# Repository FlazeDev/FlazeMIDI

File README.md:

# FlazeMIDI

This is a simple 25 key MIDI Controller with 3 rotary encoders. I used a Raspberry Pi Pico as the brain for this MIDI Controller.

## Bill of Materials (BOM)
|BOM for FlazeMIDI|FIELD2                         |FIELD3                                                                                     |FIELD4                      |FIELD5                                     |FIELD6                          |
|-----------------|-------------------------------|-------------------------------------------------------------------------------------------|----------------------------|-------------------------------------------|--------------------------------|
|S.No             |Name Of Part                   |Link                                                                                       |Price per item(W/o Shipping)|Quantity                                   |Total Cost Of Item(W/O Shipping)|
|1                |Raspberry pi pico              |https://robu.in/product/raspberry-pi-pico-with-headers/                                    |499.00 INR                  |1                                          |499.00 INR                      |
|2                |1N4148 diodes(pack of 50)      |https://www.amazon.in/gp/product/B0B53NV1QC/ref=ox_sc_act_title_1?smid=A3OFZYSBUU01KL&psc=1|99.00 INR                   |1                                          |99.00 INR                       |
|3                |Switches(pack of 10)           |https://stackskb.com/store/click-inc-hp-switch-pack-of-10-pre-order/                       |180.00 INR                  |3                                          |540.00 INR                      |
|4                |EC11 Rotary Encoders(pack of 5)|https://stackskb.com/store/click-inc-hp-switch-pack-of-10-pre-order/                       |696.00 INR                  |1                                          |696.00 INR                      |
|5                |Keycaps(pack of 5)             |https://meckeys.com/shop/accessories/keyboard-accessories/keycaps/blank-dsa-keycaps-1u/    |95.00 INR                   |5                                          |475.00 INR                      |
|6                |PCB Fabrication                |jlcpcb.com                                                                                 |976.96 INR                  |1                                          |976.96 INR                      |
|7                |PCB Shipping                   |jlcpcb.com                                                                                 |1,091.73 INR                |1                                          |1,091.73 INR                    |
|8                |M3x4mm Heatsets                |I already have it                                                                          |0.00 INR                    |4                                          |0.00 INR                        |
|9                |M3x4mm screws                  |I already have it                                                                          |0.00 INR                    |4                                          |0.00 INR                        |
|                 |                               |                                                                                           |                            |                                           |                                |
|                 |                               |                                                                                           |                            |                                           |                                |
|                 |                               |                                                                                           |                            |                                           |                                |
|                 |                               |                                                                                           |                            |                                           |                                |
|                 |                               |                                                                                           |                            |                                           |                                |
|                 |                               |                                                                                           |                            |                                           |                                |
|                 |                               |                                                                                           |                            |Total INR(only including  Shipping for pcb)|4,377.69 INR                    |
|                 |                               |                                                                                           |                            |Total USD                                  |$48.15                          |

### Total Project Cost
$48.15 without shipping. Shipping should take another $10 max.
Total Project cost: **$58**

## Schematic & PCB

I made the pcb in kicad

## 3d Case

The case consists of 3 parts, the top cover, bottom cover and a stand that attaches to the bottom. Everything is connected using m3 heat set inserts and screws.
I made the case in onshape. here's the link for the onshape project:- https://cad.onshape.com/documents/0f47473beb05ba1bc00654df/w/e1cbcdd202a0a0f5e24ed7bd/e/dbeb9d6fbd234f685e1c68c6

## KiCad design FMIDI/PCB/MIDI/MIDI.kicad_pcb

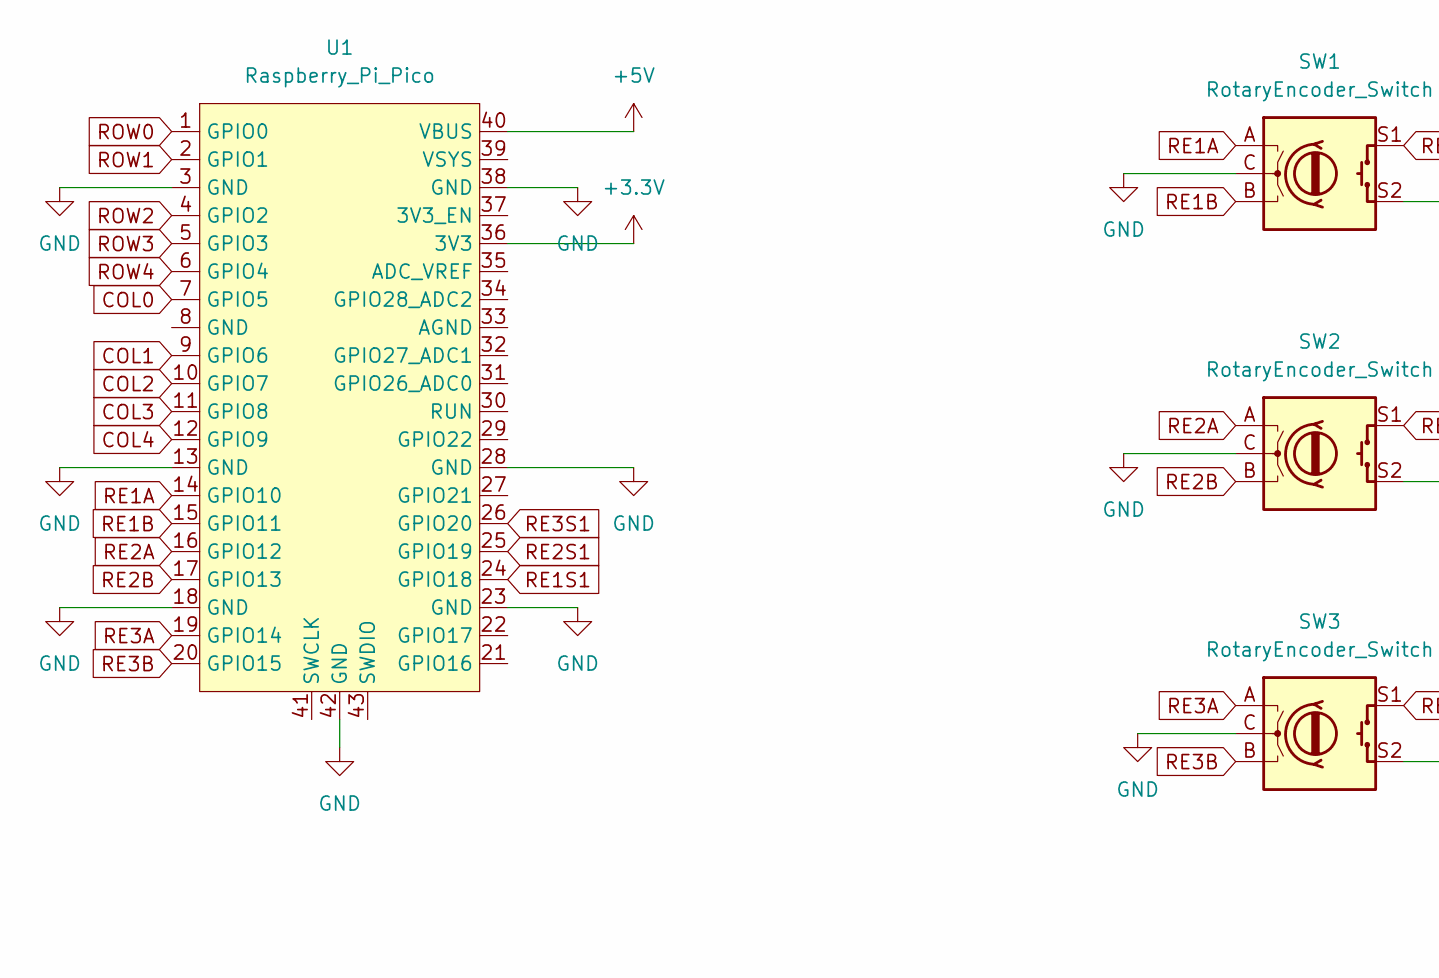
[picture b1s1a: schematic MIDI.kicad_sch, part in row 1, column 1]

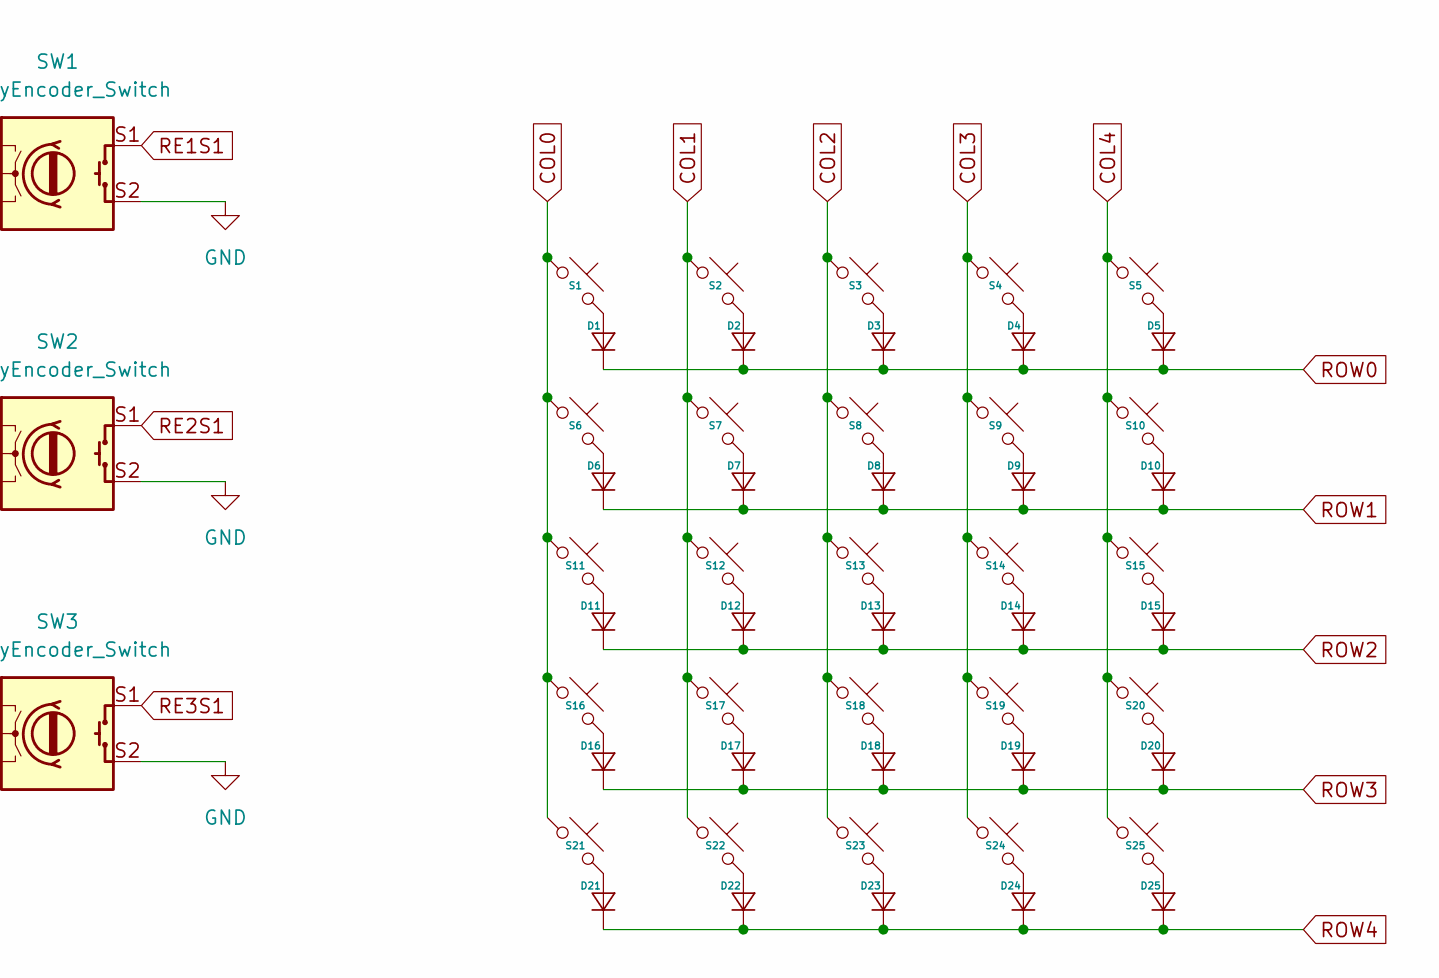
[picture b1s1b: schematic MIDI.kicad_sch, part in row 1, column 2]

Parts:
D1, D2, D3, D4, D5, D6, D7, D8, D9, D10, D11, D12, D13, D14, D15, D16, D17, D18, D19, D20, D21, D22, D23, D24, D25: D_DO-35_SOD27_P7.62mm_Horizontal
S1, S2, S3, S4, S5, S6, S7, S8, S9, S10, S11, S12, S13, S14, S15, S16, S17, S18, S19, S20, S21, S22, S23, S24, S25: MX_PCB_1.00u
SW1, SW2, SW3: RotaryEncoder_Switch; Encoder_EC11_MX
U1: Raspberry_Pi_Pico

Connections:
+3.3V: U1.36 (3V3)
+5V: U1.40 (VBUS)
COL0: S1.1, S6.1, S11.1, S16.1, S21.1, U1.7 (GPIO5)
COL1: S2.1, S7.1, S12.1, S17.1, S22.1, U1.9 (GPIO6)
COL2: S3.1, S8.1, S13.1, S18.1, S23.1, U1.10 (GPIO7)
COL3: S4.1, S9.1, S14.1, S19.1, S24.1, U1.11 (GPIO8)
COL4: S5.1, S10.1, S15.1, S20.1, S25.1, U1.12 (GPIO9)
GND: SW1.C, SW1.S2, SW2.C, SW2.S2, SW3.C, SW3.S2, U1.3 (GND), U1.13 (GND), U1.18 (GND), U1.23 (GND), U1.28 (GND), U1.38 (GND), U1.42 (GND)
unnamed: D1.2 (A), S1.2
unnamed: D2.2 (A), S2.2
unnamed: D3.2 (A), S3.2
unnamed: D4.2 (A), S4.2
unnamed: D5.2 (A), S5.2
unnamed: D6.2 (A), S6.2
unnamed: D7.2 (A), S7.2
unnamed: D8.2 (A), S8.2
unnamed: D9.2 (A), S9.2
unnamed: D10.2 (A), S10.2
unnamed: D11.2 (A), S11.2
unnamed: D12.2 (A), S12.2
unnamed: D13.2 (A), S13.2
unnamed: D14.2 (A), S14.2
unnamed: D15.2 (A), S15.2
unnamed: D16.2 (A), S16.2
unnamed: D17.2 (A), S17.2
unnamed: D18.2 (A), S18.2
unnamed: D19.2 (A), S19.2
unnamed: D20.2 (A), S20.2
unnamed: D21.2 (A), S21.2
unnamed: D22.2 (A), S22.2
unnamed: D23.2 (A), S23.2
unnamed: D24.2 (A), S24.2
unnamed: D25.2 (A), S25.2
RE1A: SW1.A, U1.14 (GPIO10)
RE1B: SW1.B, U1.15 (GPIO11)
RE1S1: SW1.S1, U1.24 (GPIO18)
RE2A: SW2.A, U1.16 (GPIO12)
RE2B: SW2.B, U1.17 (GPIO13)
RE2S1: SW2.S1, U1.25 (GPIO19)
RE3A: SW3.A, U1.19 (GPIO14)
RE3B: SW3.B, U1.20 (GPIO15)
RE3S1: SW3.S1, U1.26 (GPIO20)
ROW0: D1.1 (K), D2.1 (K), D3.1 (K), D4.1 (K), D5.1 (K), U1.1 (GPIO0)
ROW1: D6.1 (K), D7.1 (K), D8.1 (K), D9.1 (K), D10.1 (K), U1.2 (GPIO1)
ROW2: D11.1 (K), D12.1 (K), D13.1 (K), D14.1 (K), D15.1 (K), U1.4 (GPIO2)
ROW3: D16.1 (K), D17.1 (K), D18.1 (K), D19.1 (K), D20.1 (K), U1.5 (GPIO3)
ROW4: D21.1 (K), D22.1 (K), D23.1 (K), D24.1 (K), D25.1 (K), U1.6 (GPIO4)

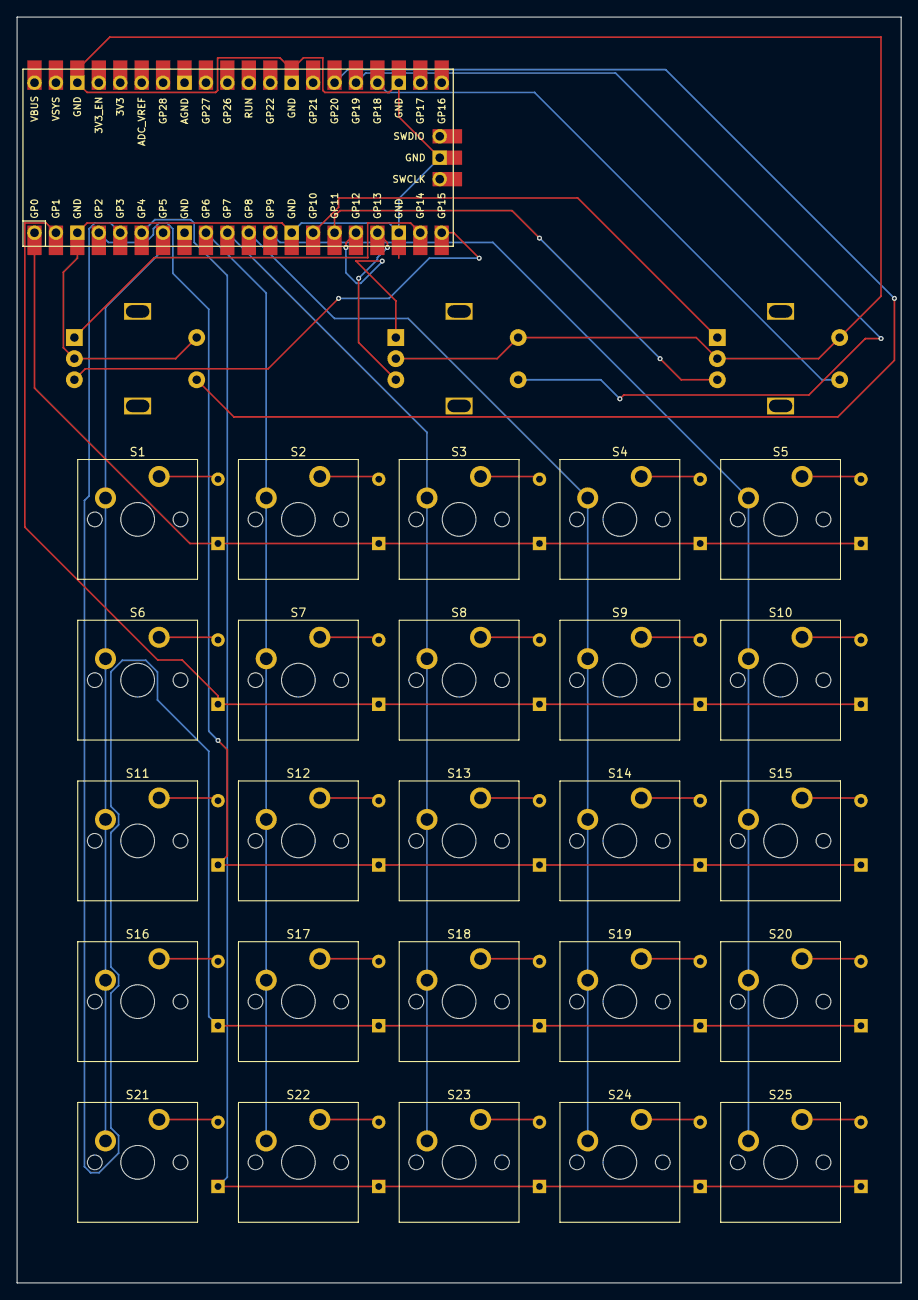
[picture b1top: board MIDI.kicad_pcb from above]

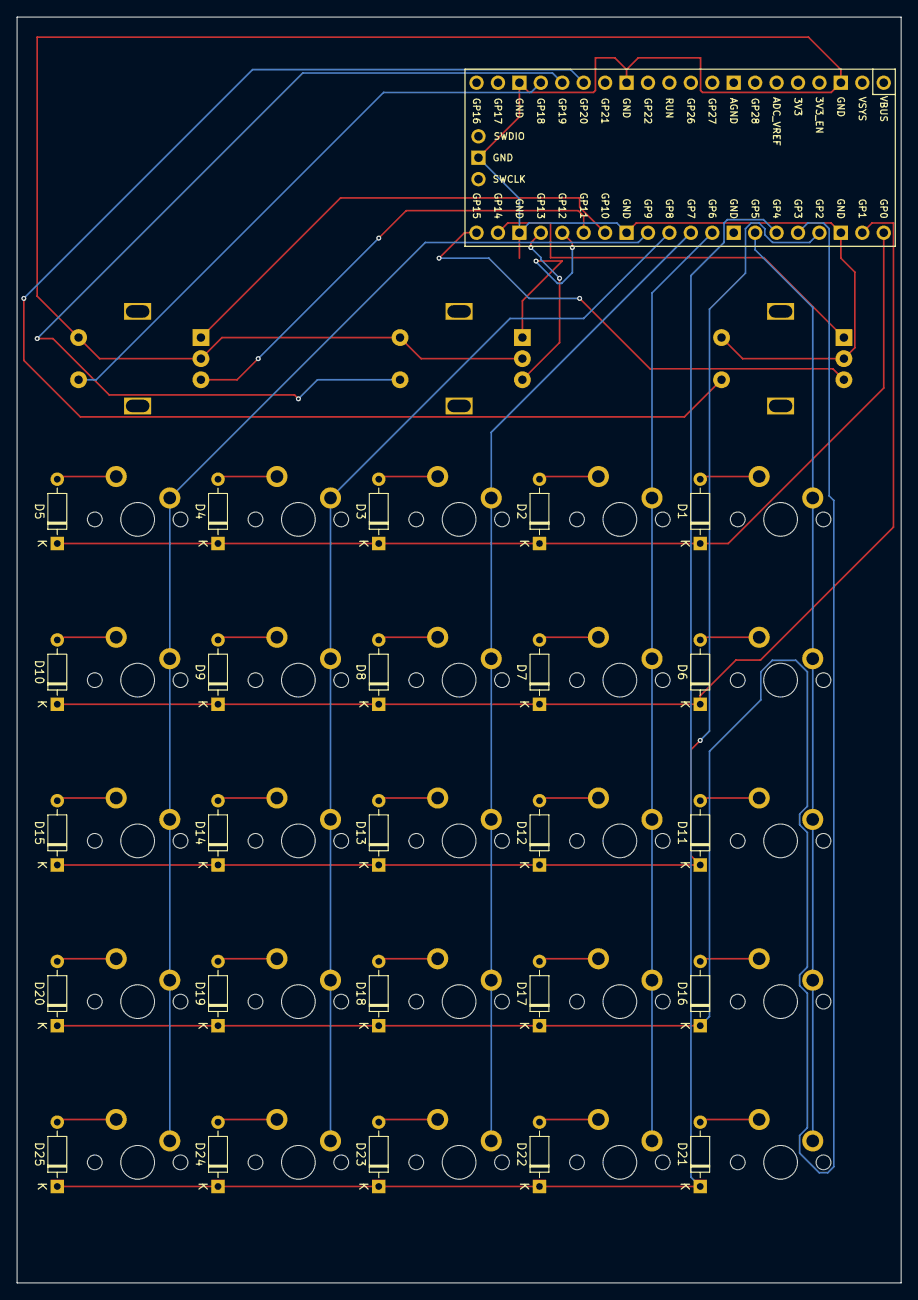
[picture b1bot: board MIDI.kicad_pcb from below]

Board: 2 copper layers, 104.8 x 150.0 mm, 54 parts (25 on the bottom side), 45 nets.

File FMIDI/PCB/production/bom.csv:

Designator,Footprint,Quantity,Value,LCSC Part #
"D1, D10, D11, D12, D13, D14, D15, D16, D17, D18, D19, D2, D20, D21, D22, D23, D24, D25, D3, D4, D5, D6, D7, D8, D9",D_DO-35_SOD27_P7.62mm_Horizontal,25,~,
"S1, S10, S11, S12, S13, S14, S15, S16, S17, S18, S19, S2, S20, S21, S22, S23, S24, S25, S3, S4, S5, S6, S7, S8, S9",MX_PCB_1.00u,25,~,
"SW1, SW2, SW3",Encoder_EC11_MX,3,RotaryEncoder_Switch,
U1,Raspberry_Pi_Pico,1,Raspberry_Pi_Pico,

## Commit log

2026-03-29 Commit 1
2026-04-03 V2.1
2026-04-03 V2.2
